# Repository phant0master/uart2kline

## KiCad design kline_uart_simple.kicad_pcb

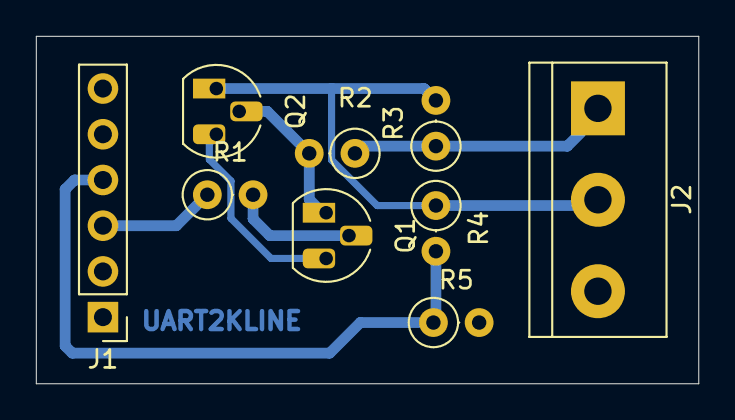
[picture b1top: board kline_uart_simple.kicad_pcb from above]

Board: 4 copper layers, 36.8 x 19.3 mm, 9 parts (0 on the bottom side), 7 nets.

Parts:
J1: USB2UART; PinHeader_1x06_P2.54mm_Vertical
J2: KLINE_CONN; TerminalBlock_bornier-3_P5.08mm
Q1, Q2: BC547; TO-92_HandSolder
R1: 1K; R_Axial_DIN0207_L6.3mm_D2.5mm_P2.54mm_Vertical
R2, R3: 470R; R_Axial_DIN0207_L6.3mm_D2.5mm_P2.54mm_Vertical
R4: 100K; R_Axial_DIN0207_L6.3mm_D2.5mm_P2.54mm_Vertical
R5: 47k; R_Axial_DIN0207_L6.3mm_D2.5mm_P2.54mm_Vertical

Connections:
+12V: J2.1, R2.1, R3.1
GND: J1.2, J2.3, Q1.3, Q2.3, R5.2
KLINE: J2.2, Q2.1, R3.2, R4.1
unnamed: Q1.1, Q2.2, R2.2
unnamed: Q1.2, R1.2
RX_I: J1.4, R4.2, R5.1
TX_O: J1.3, R1.1

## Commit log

2022-03-08 new output pdf
2022-03-09 Updated to kicad 6.0.2
2022-03-09 New output files
